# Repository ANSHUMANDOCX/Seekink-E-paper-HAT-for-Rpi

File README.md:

# Seekink-E-paper-HAT-for-Rpi
This a HAT for a epaper display for SEEKINK displays with raspberry pi Also can be used with any oher MCU using the 9 in connector. It supports multiple Displays of almost every Size

## Parts
- Raspberry Pi Zero 2 W
- 3.7 inch Epaper Display

## Plan
I needed a HAT that could be used with a Cheap Epaper dispaly paired with a raspberry pi. I found one on LCSC but it didnt have a HAT of that wa 100% compatible with it. 
So, i took reference from existing HATs and the Datasheet of the Epaper Display and made my own that could be attatched on top of raspberry pi WH.
I also added a 9 pin connector and a Voltage Level shifter so that i can connect it to most of the microcontrollers.

It can be programmed using the GxEPD2 Library
## PCB

## BOM
| S.No | Product Code | Description                       | Quantity | Total Price | Supplier | Category            |LINK|
|------|--------------|-----------------------------------|----------|-------------|----------|---------------------|-------------------------------|
| 1    | C500051      | SK-3296S-01-L2 Slide Switch       | 5        | $0.39       | LCSC     | Passive Components  |https://lcsc.com/product-detail/Slide-Switches_XKB-Connection-SK-3296S-01-L2_C500051.html?s_z=n_C500051|
| 2    | C5224028     | PM2.54-1*9 Female Header (1x9P)   | 5        | $0.52       | LCSC     | Connectors          |https://lcsc.com/product-detail/Female-Headers_ZHOURI-PM2-54-1-9_C5224028.html?s_z=n_C5224028%2509|
| 3    | C2977589     | 2.54-2*20 Female Header (2x20P)   | 5        | $0.97       | LCSC     | Connectors          |https://lcsc.com/product-detail/Female-Headers_ZHOURI-2-54-2-20_C2977589.html?s_z=n_C2977589|
| 4    | C53406       | TXB0108PWR Level Shifter          | 5        | $1.25       | LCSC     | ICs                 |https://lcsc.com/product-detail/Translators-Level-Shifters_Texas-Instruments-TXB0108PWR_C53406.html?s_z=n_C53406|
| 5    | C41416467    | SEEKINK E037A49 E-Ink Display     | 1        | $7.22       | LCSC     | Display             |https://lcsc.com/product-detail/E-ink-Display_SEEKINK-E037A49_C41416467.html?s_z=n_C41416467|
| 6    | —            | 0603 Resistors (47kΩ + 3Ω total)  | —        | $0.25       | LCSC     | Passive Components  |https://lcsc.com/product-detail/Chip-Resistor-Surface-Mount_FOJAN-FRC0603F3R00TS_C2930150.html  https://lcsc.com/product-detail/Chip-Resistor-Surface-Mount_YAGEO-RC0603FR-0747KL_C105579.html|
|||Shipping||3.75|LCSC|||
|      |              | **Total**                         |          |14.52|        |                     |
|||Raspberry Pi zero 2 W+ adapters                        |          |20            |Silverline||https://www.silverlineelectronics.in/products/raspberry-pi-zero-2-silverline-india-authorised-distributor?variant=41596564144297   https://www.silverlineelectronics.in/products/usb-b-male-to-usb-a-female-otg-adaptor-official?variant=41014335176873  https://www.silverlineelectronics.in/products/official-raspberry-pi-micro-sd-card-adapter?variant=41020736995497|
|||PCB+ Shipping||12|JLCPCB|||
|||**TOTAL**||42|||

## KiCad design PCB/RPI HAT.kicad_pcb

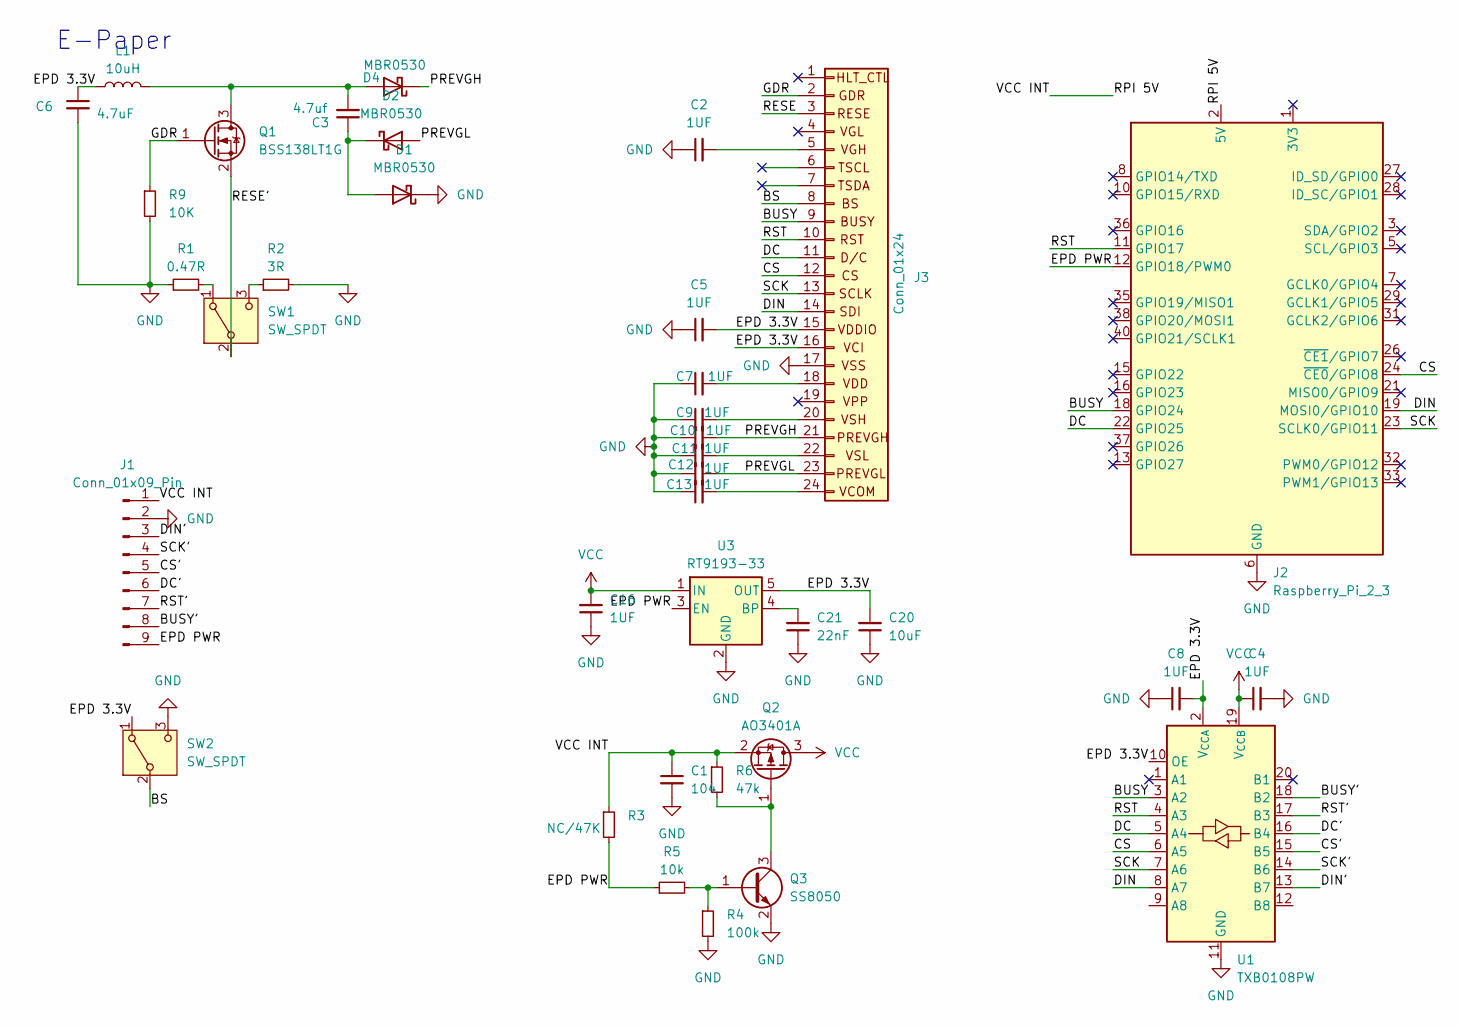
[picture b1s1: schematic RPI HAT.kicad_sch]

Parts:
C1: 104; C_0603_1608Metric
C2, C4, C5, C7, C8, C9, C10, C11, C12, C13, C16: 1UF; C_0603_1608Metric_Pad1.08x0.95mm_HandSolder
C3: 4.7uf; C_0603_1608Metric_Pad1.08x0.95mm_HandSolder
C6: 4.7uF; C_0603_1608Metric_Pad1.08x0.95mm_HandSolder
C20: 10uF; C_0603_1608Metric_Pad1.08x0.95mm_HandSolder
C21: 22nF; C_0603_1608Metric_Pad1.08x0.95mm_HandSolder
D1, D2, D4: MBR0530; D_SOD-123
J1: Conn_01x09_Pin; PinHeader_1x09_P2.54mm_Vertical
J2: Raspberry_Pi_2_3; PinHeader_2x20_P2.54mm_Vertical
J3: Conn_01x24; Hirose_FH12-24S-0.5SH_1x24-1MP_P0.50mm_Horizontal
L1: 10uH; L_Changjiang_FNR4020S
Q1: BSS138LT1G; SOT-23
Q2: AO3401A; SOT-23
Q3: SS8050; SOT-23
R1: 0.47R; R_0603_1608Metric_Pad0.98x0.95mm_HandSolder
R2: 3R; R_0603_1608Metric_Pad0.98x0.95mm_HandSolder
R3: NC/47K; R_0603_1608Metric_Pad0.98x0.95mm_HandSolder
R4: 100k; R_0603_1608Metric_Pad0.98x0.95mm_HandSolder
R5: 10k; R_0603_1608Metric_Pad0.98x0.95mm_HandSolder
R6: 47k; R_0603_1608Metric_Pad0.98x0.95mm_HandSolder
R9: 10K; R_0603_1608Metric_Pad0.98x0.95mm_HandSolder
SW1, SW2: SW_SPDT; SW-SMD_SK-3296S-01-L2
U1: TXB0108PW; TSSOP-20_4.4x6.5mm_P0.65mm
U3: RT9193-33; SOT-23-5

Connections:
/BS: J3.8, SW2.2 (B); also elsewhere on the board
/BUSY: J2.18 (GPIO24), J3.9, U1.3 (A2)
/BUSY': J1.8, U1.18 (B2)
/CS: J2.24 (~CE0/GPIO8), J3.12, U1.6 (A5)
/CS': J1.5, U1.15 (B5)
/DC: J2.22 (GPIO25), J3.11, U1.5 (A4)
/DC': J1.6, U1.16 (B4)
/DIN: J2.19 (MOSI0/GPIO10), J3.14, U1.8 (A7)
/DIN': J1.3, U1.13 (B7)
/EPD 3.3V: C5.2, C6.1, C8.2, C20.2, J3.15, J3.16, L1.1, SW2.1 (A), U1.2 (V_{CCA}), U1.10 (OE), U3.5 (OUT); also elsewhere on the board
/EPD PWR: J1.9, J2.12 (GPIO18/PWM0), R3.2, R5.1, U3.3 (EN)
/GDR: J3.2, Q1.1 (G), R9.1
/PREVGH: C10.2, D4.1 (K), J3.21
/PREVGL: C12.2, D2.2 (A), J3.23
/RESE: J3.3
/RESE': Q1.2 (S), SW1.2 (B)
/RPI 5V: C1.1, J1.1, J2.2 (5V), J2.4 (5V), Q2.2 (S), R3.1, R6.1
/RST: J2.11 (GPIO17), J3.10, U1.4 (A3)
/RST': J1.7, U1.17 (B3)
/SCK: J2.23 (SCLK0/GPIO11), J3.13, U1.7 (A6)
/SCK': J1.4, U1.14 (B6)
GND: C1.2, C2.1, C4.2, C5.1, C6.2, C7.1, C8.1, C9.1, C10.1, C11.1, C12.1, C13.1, C16.1, C20.1, C21.1, D1.1 (K), J1.2, J2.6 (GND), J2.9 (GND), J2.14 (GND), J2.20 (GND), J2.25 (GND), J2.30 (GND), J2.34 (GND), J2.39 (GND), J3.17, Q3.2 (E), R1.1, R2.2, R4.2, R9.2, SW2.3 (C), U1.11 (GND), U3.2 (GND); also elsewhere on the board
unnamed: C3.1, D1.2 (A), D2.1 (K)
unnamed: C3.2, D4.2 (A), L1.2, Q1.3 (D)
unnamed: C2.2, J3.5
unnamed: C7.2, J3.18
unnamed: C9.2, J3.20
unnamed: C11.2, J3.22
unnamed: C13.2, J3.24
unnamed: Q2.1 (G), Q3.3 (C), R6.2
unnamed: Q3.1 (B), R4.1, R5.2
unnamed: R1.2, SW1.1 (A)
unnamed: R2.1, SW1.3 (C)
unnamed: C21.2, U3.4 (BP)
VCC: C4.1, C16.2, Q2.3 (D), U1.19 (V_{CCB}), U3.1 (IN)

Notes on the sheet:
E-Paper

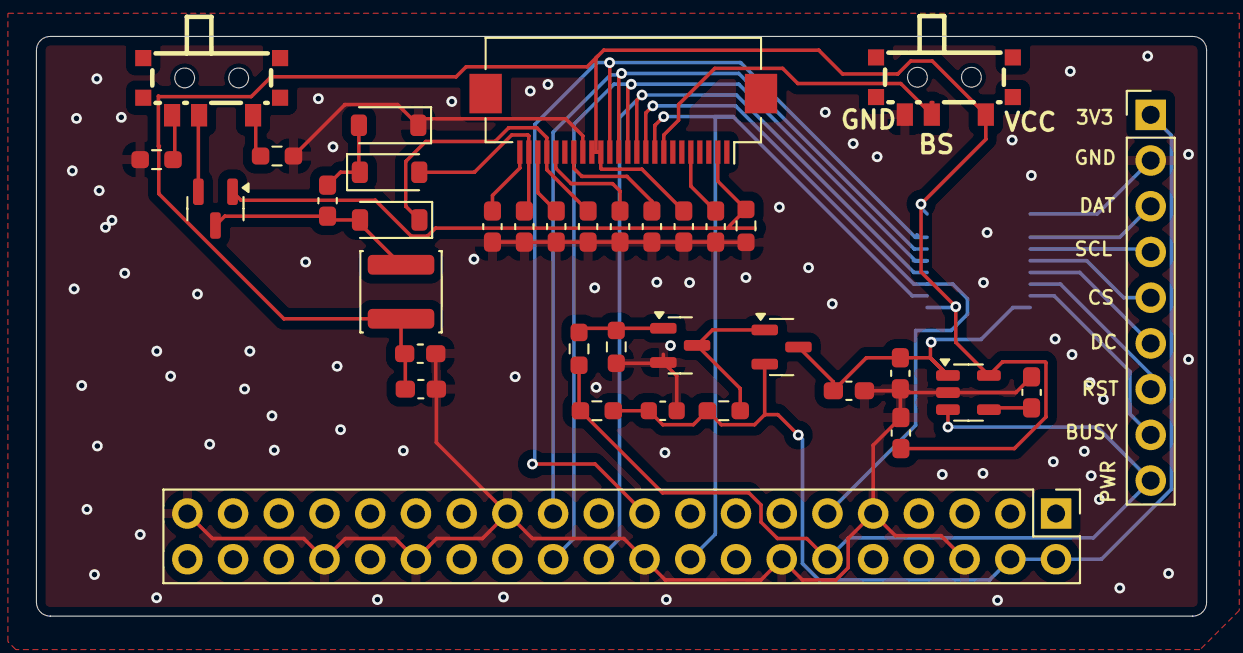
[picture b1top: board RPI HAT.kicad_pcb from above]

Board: 2 copper layers, 65.0 x 32.2 mm, 37 parts (1 on the bottom side), 34 nets.

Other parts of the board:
BS: SW_SPDT; SW-SMD_SK-3296S-01-L2

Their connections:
/BS: BS.2 (B); also elsewhere on the board
/EPD 3.3V: BS.1 (A); also elsewhere on the board
GND: BS.3 (C); also elsewhere on the board

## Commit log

2025-08-01 Update README.md
    forgot to add the shipping
